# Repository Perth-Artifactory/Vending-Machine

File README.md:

# Vending-Machine
Member can vending machine

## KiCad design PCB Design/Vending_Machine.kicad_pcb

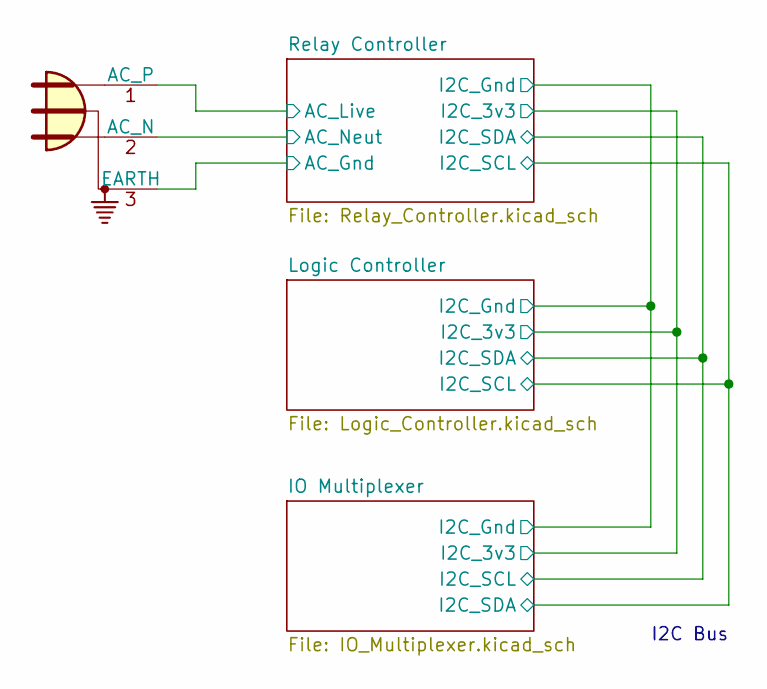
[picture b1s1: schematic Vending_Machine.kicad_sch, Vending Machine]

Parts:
P01: Main Supply

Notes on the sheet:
I2C Bus

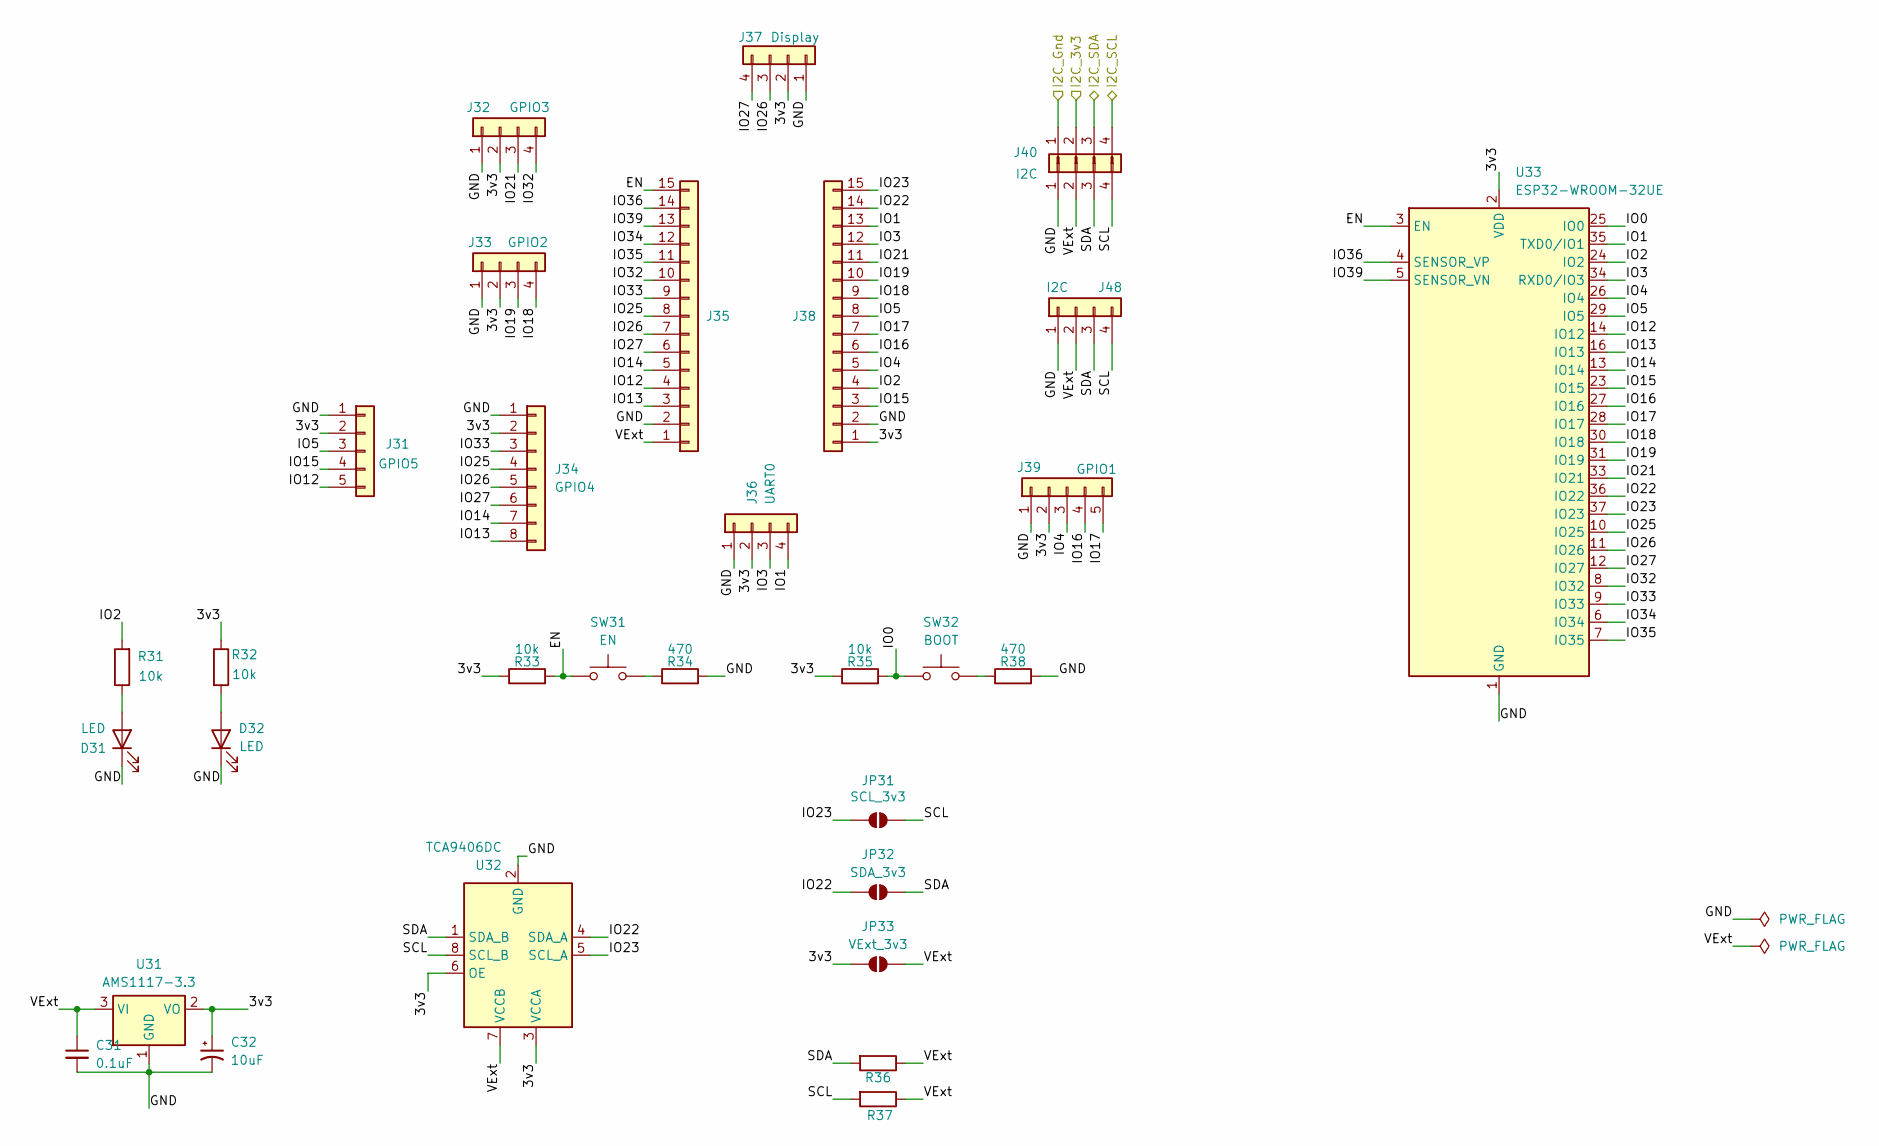
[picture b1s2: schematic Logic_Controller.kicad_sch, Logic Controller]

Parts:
C31: 0.1uF; C_0805_2012Metric_Pad1.18x1.45mm_HandSolder
C32: 10uF; C_0805_2012Metric_Pad1.18x1.45mm_HandSolder
D31, D32: LED; LED_0805_2012Metric_Pad1.15x1.40mm_HandSolder
J31: GPIO5; JST_XH_B5B-XH-A_1x05_P2.50mm_Vertical
J32: GPIO3; JST_XH_B4B-XH-A_1x04_P2.50mm_Vertical
J33: GPIO2; JST_XH_B4B-XH-A_1x04_P2.50mm_Vertical
J34: GPIO4; JST_XH_B8B-XH-A_1x08_P2.50mm_Vertical
J35, J38: Conn_01x15; PinHeader_1x15_P2.54mm_Vertical
J36: UART0; JST_XH_B4B-XH-A_1x04_P2.50mm_Vertical
J37: Display; PinHeader_1x04_P2.54mm_Vertical
J39: GPIO1; JST_XH_B5B-XH-A_1x05_P2.50mm_Vertical
J40, J48: I2C; JST_XH_B4B-XH-A_1x04_P2.50mm_Vertical
J44: Conn_01x04_Pin
JP31: SCL_3v3; SolderJumper-2_P1.3mm_Open_RoundedPad1.0x1.5mm
JP32: SDA_3v3; SolderJumper-2_P1.3mm_Open_RoundedPad1.0x1.5mm
JP33: VExt_3v3; SolderJumper-2_P1.3mm_Open_RoundedPad1.0x1.5mm
R31, R32, R33, R35: 10k; R_0805_2012Metric_Pad1.20x1.40mm_HandSolder
R34, R38: 470; R_0805_2012Metric_Pad1.20x1.40mm_HandSolder
R36, R37: R; R_0805_2012Metric_Pad1.20x1.40mm_HandSolder
SW31: EN; SW_Push_SPST_NO_Alps_SKRK
SW32: BOOT; SW_Push_SPST_NO_Alps_SKRK
U31: AMS1117-3.3; SOT-223-3_TabPin2
U32: TCA9406DC; VSSOP-8_2.3x2mm_P0.5mm
U33: ESP32-WROOM-32UE

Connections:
/Logic Controller/3v3: C32.1, J31.2, J32.2, J33.2, J34.2, J36.2, J37.2, J38.1, J39.2, JP33.1 (A), R32.1, R33.1, R35.1, U31.2 (VO), U32.3 (VCCA), U32.6 (OE), U33.2 (VDD)
/Logic Controller/EN: J35.15, R33.2, SW31.1, U33.3 (EN)
/Logic Controller/GND: C31.2, C32.2, D31.1 (K), D32.1 (K), J31.1, J32.1, J33.1, J34.1, J35.2, J36.1, J37.1, J38.2, J39.1, J40.1, J48.1, R34.2, R38.2, U31.1 (GND), U32.2 (GND), U33.1 (GND), U33.15 (GND), U33.38 (GND), U33.39 (GND); also elsewhere on the board
/Logic Controller/IO0: R35.2, SW32.1, U33.25 (IO0)
/Logic Controller/IO1: J36.4, J38.13, U33.35 (TXD0/IO1)
/Logic Controller/IO2: J38.4, R31.2, U33.24 (IO2)
/Logic Controller/IO3: J36.3, J38.12, U33.34 (RXD0/IO3)
/Logic Controller/IO4: J38.5, J39.3, U33.26 (IO4)
/Logic Controller/IO5: J31.3, J38.8, U33.29 (IO5)
/Logic Controller/IO12: J31.5, J35.4, U33.14 (IO12)
/Logic Controller/IO13: J34.8, J35.3, U33.16 (IO13)
/Logic Controller/IO14: J34.7, J35.5, U33.13 (IO14)
/Logic Controller/IO15: J31.4, J38.3, U33.23 (IO15)
/Logic Controller/IO16: J38.6, J39.4, U33.27 (IO16)
/Logic Controller/IO17: J38.7, J39.5, U33.28 (IO17)
/Logic Controller/IO18: J33.4, J38.9, U33.30 (IO18)
/Logic Controller/IO19: J33.3, J38.10, U33.31 (IO19)
/Logic Controller/IO21: J32.3, J38.11, U33.33 (IO21)
/Logic Controller/IO22: J38.14, JP32.1 (A), U32.4 (SDA_A), U33.36 (IO22)
/Logic Controller/IO23: J38.15, JP31.1 (A), U32.5 (SCL_A), U33.37 (IO23)
/Logic Controller/IO25: J34.4, J35.8, U33.10 (IO25)
/Logic Controller/IO26: J34.5, J35.7, J37.3, U33.11 (IO26)
/Logic Controller/IO27: J34.6, J35.6, J37.4, U33.12 (IO27)
/Logic Controller/IO32: J32.4, J35.10, U33.8 (IO32)
/Logic Controller/IO33: J34.3, J35.9, U33.9 (IO33)
/Logic Controller/IO34: J35.12, U33.6 (IO34)
/Logic Controller/IO35: J35.11, U33.7 (IO35)
/Logic Controller/IO36: J35.14, U33.4 (SENSOR_VP)
/Logic Controller/IO39: J35.13, U33.5 (SENSOR_VN)
/Logic Controller/SCL: J40.4, J48.4, JP31.2 (B), R37.2, U32.8 (SCL_B)
/Logic Controller/SDA: J40.3, J48.3, JP32.2 (B), R36.2, U32.1 (SDA_B)
/Logic Controller/VExt: C31.1, J35.1, J40.2, J48.2, JP33.2 (B), R36.1, R37.1, U31.3 (VI), U32.7 (VCCB)
unnamed: D31.2 (A), R31.1
unnamed: D32.2 (A), R32.2
unnamed: R34.1, SW31.2
unnamed: R38.1, SW32.2

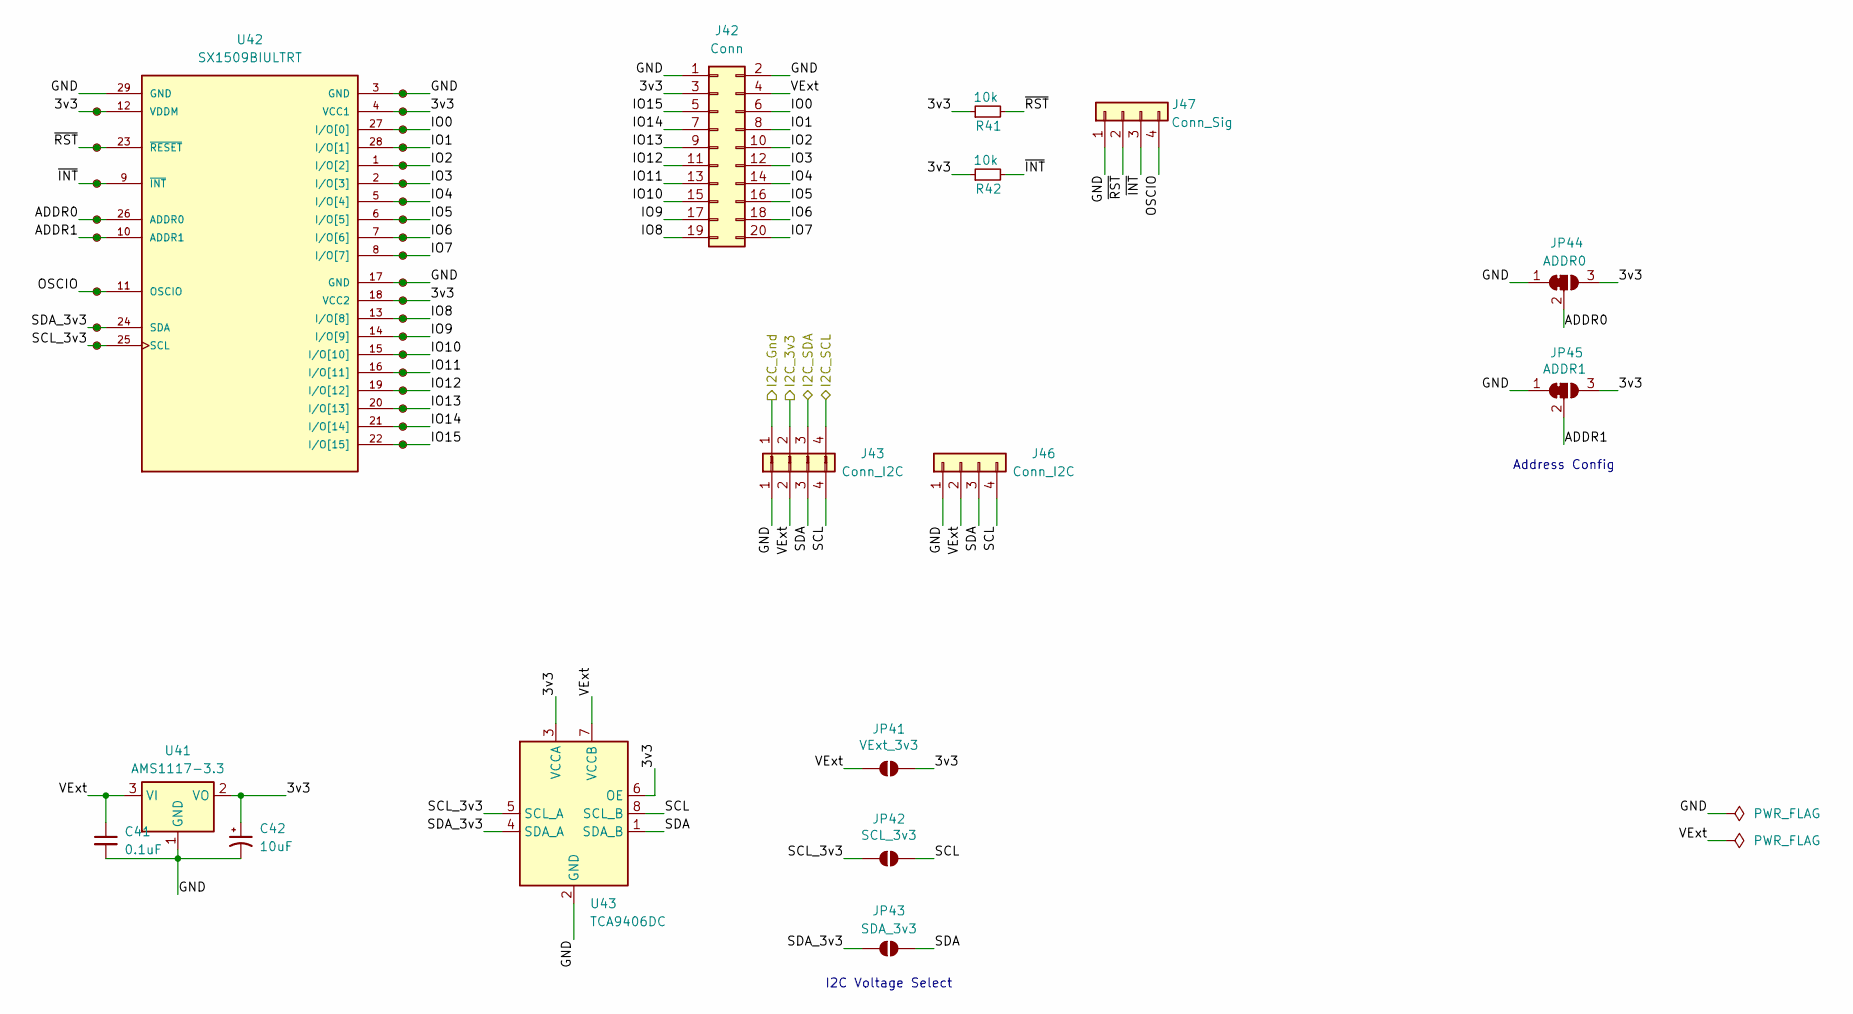
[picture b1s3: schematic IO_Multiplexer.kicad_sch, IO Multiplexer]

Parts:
C41: 0.1uF; C_0805_2012Metric_Pad1.18x1.45mm_HandSolder
C42: 10uF; C_0805_2012Metric_Pad1.18x1.45mm_HandSolder
J42: Conn; IDC-Header_2x10_P2.54mm_Vertical
J43, J46: Conn_I2C; JST_XH_B4B-XH-A_1x04_P2.50mm_Vertical
J45: Conn_01x04_Pin
J47: Conn_Sig; PinHeader_1x04_P2.54mm_Vertical
JP41: VExt_3v3; SolderJumper-2_P1.3mm_Open_RoundedPad1.0x1.5mm
JP42: SCL_3v3; SolderJumper-2_P1.3mm_Open_RoundedPad1.0x1.5mm
JP43: SDA_3v3; SolderJumper-2_P1.3mm_Open_RoundedPad1.0x1.5mm
JP44: ADDR0; SolderJumper-3_P1.3mm_Bridged12_RoundedPad1.0x1.5mm_NumberL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
JP45: ADDR1; SolderJumper-3_P1.3mm_Bridged12_RoundedPad1.0x1.5mm_NumberL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
R41, R42: 10k; R_0805_2012Metric_Pad1.20x1.40mm_HandSolder
TP39, TP48, TP58: 3v3; TestPoint_Pad_D1.0mm
TP40: ~{RST}; TestPoint_Pad_D1.0mm
TP41: ~{INT}; TestPoint_Pad_D1.0mm
TP42: Addr0; TestPoint_Pad_D1.0mm
TP43: Addr1; TestPoint_Pad_D1.0mm
TP44: OSC; TestPoint_Pad_D1.0mm
TP45: SDA; TestPoint_Pad_D1.0mm
TP46: SCL; TestPoint_Pad_D1.0mm
TP47, TP57: GND; TestPoint_Pad_D1.0mm
TP49: IO0; TestPoint_Pad_D1.0mm
TP50: IO1; TestPoint_Pad_D1.0mm
TP51: IO2; TestPoint_Pad_D1.0mm
TP52: IO3; TestPoint_Pad_D1.0mm
TP53: IO4; TestPoint_Pad_D1.0mm
TP54: IO5; TestPoint_Pad_D1.0mm
TP55: IO6; TestPoint_Pad_D1.0mm
TP56: IO7; TestPoint_Pad_D1.0mm
TP59: IO8; TestPoint_Pad_D1.0mm
TP60: IO9; TestPoint_Pad_D1.0mm
TP61: IO10; TestPoint_Pad_D1.0mm
TP62: IO11; TestPoint_Pad_D1.0mm
TP63: IO12; TestPoint_Pad_D1.0mm
TP64: IO13; TestPoint_Pad_D1.0mm
TP65: IO14; TestPoint_Pad_D1.0mm
TP66: IO15; TestPoint_Pad_D1.0mm
U41: AMS1117-3.3; SOT-223-3_TabPin2
U42: SX1509BIULTRT; QFN-28-1EP_4x4mm_P0.4mm_EP2.6x2.6mm_ThermalVias; PARTREV Rev 4 – 26th April 2011
U43: TCA9406DC; VSSOP-8_2.3x2mm_P0.5mm

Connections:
/IO Multiplexer/3v3: C42.1, J42.3, JP41.2 (B), JP44.3 (B), JP45.3 (B), R41.1, R42.1, TP39.1, TP48.1, TP58.1, U41.2 (VO), U42.4 (VCC1), U42.12 (VDDM), U42.18 (VCC2), U43.3 (VCCA), U43.6 (OE)
/IO Multiplexer/ADDR0: JP44.2 (C), TP42.1, U42.26 (ADDR0)
/IO Multiplexer/ADDR1: JP45.2 (C), TP43.1, U42.10 (ADDR1)
/IO Multiplexer/GND: C41.2, C42.2, J42.1, J42.2, J43.1, J46.1, J47.1, JP44.1 (A), JP45.1 (A), TP47.1, TP57.1, U41.1 (GND), U42.3 (GND), U42.17 (GND), U42.29 (GND), U43.2 (GND); also elsewhere on the board
/IO Multiplexer/IO0: J42.6, TP49.1, U42.27 (I/O[0])
/IO Multiplexer/IO1: J42.8, TP50.1, U42.28 (I/O[1])
/IO Multiplexer/IO2: J42.10, TP51.1, U42.1 (I/O[2])
/IO Multiplexer/IO3: J42.12, TP52.1, U42.2 (I/O[3])
/IO Multiplexer/IO4: J42.14, TP53.1, U42.5 (I/O[4])
/IO Multiplexer/IO5: J42.16, TP54.1, U42.6 (I/O[5])
/IO Multiplexer/IO6: J42.18, TP55.1, U42.7 (I/O[6])
/IO Multiplexer/IO7: J42.20, TP56.1, U42.8 (I/O[7])
/IO Multiplexer/IO8: J42.19, TP59.1, U42.13 (I/O[8])
/IO Multiplexer/IO9: J42.17, TP60.1, U42.14 (I/O[9])
/IO Multiplexer/IO10: J42.15, TP61.1, U42.15 (I/O[10])
/IO Multiplexer/IO11: J42.13, TP62.1, U42.16 (I/O[11])
/IO Multiplexer/IO12: J42.11, TP63.1, U42.19 (I/O[12])
/IO Multiplexer/IO13: J42.9, TP64.1, U42.20 (I/O[13])
/IO Multiplexer/IO14: J42.7, TP65.1, U42.21 (I/O[14])
/IO Multiplexer/IO15: J42.5, TP66.1, U42.22 (I/O[15])
/IO Multiplexer/OSCIO: J47.4, TP44.1, U42.11 (OSCIO)
/IO Multiplexer/SCL: J43.4, J46.4, JP42.2 (B), U43.8 (SCL_B)
/IO Multiplexer/SCL_3v3: JP42.1 (A), TP46.1, U42.25 (SCL), U43.5 (SCL_A)
/IO Multiplexer/SDA: J43.3, J46.3, JP43.2 (B), U43.1 (SDA_B)
/IO Multiplexer/SDA_3v3: JP43.1 (A), TP45.1, U42.24 (SDA), U43.4 (SDA_A)
/IO Multiplexer/VExt: C41.1, J42.4, J43.2, J46.2, JP41.1 (A), U41.3 (VI), U43.7 (VCCB)
/IO Multiplexer/~INT: J47.3, R42.2, TP41.1, U42.9 (~INT)
/IO Multiplexer/~RST: J47.2, R41.2, TP40.1, U42.23 (~RESET)

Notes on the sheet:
I2C Voltage Select
Address Config

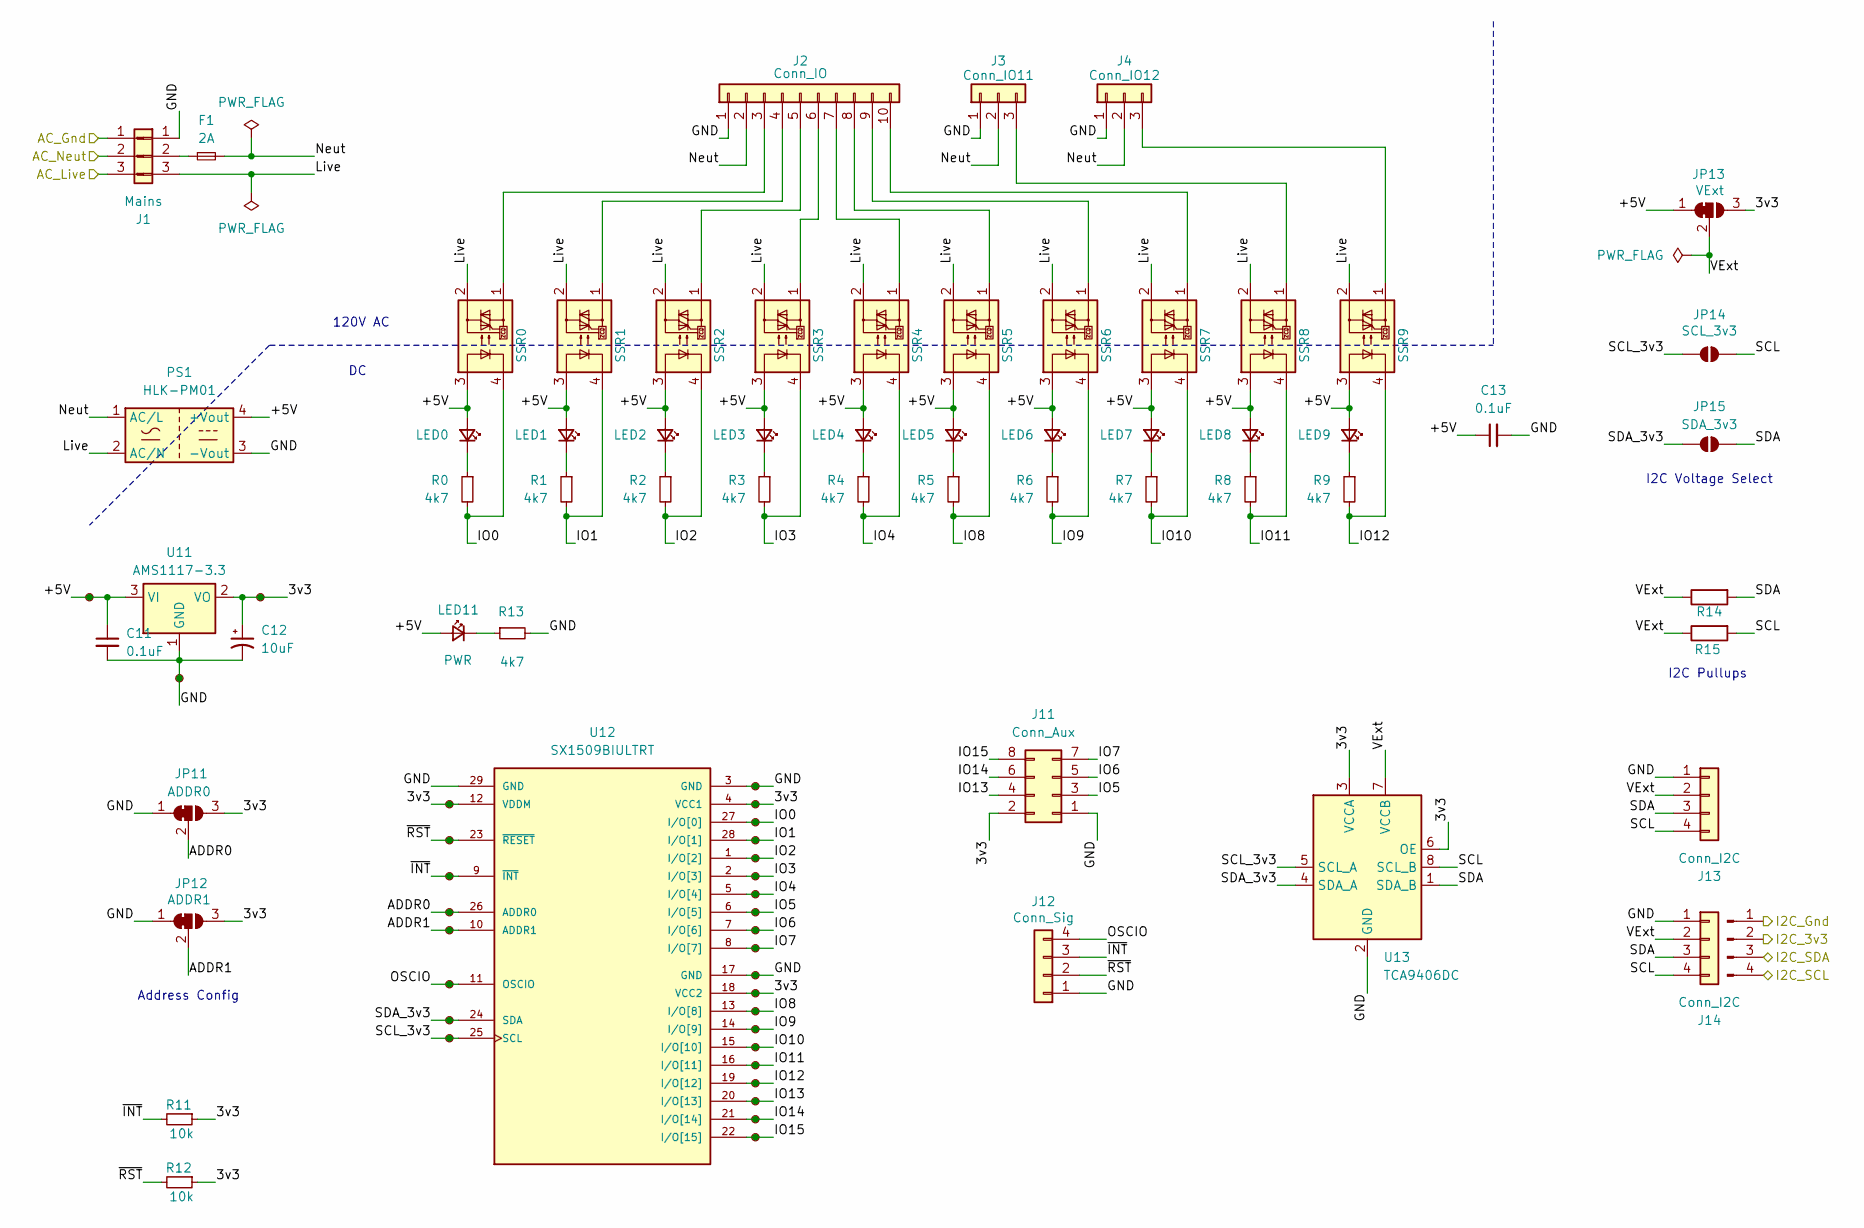
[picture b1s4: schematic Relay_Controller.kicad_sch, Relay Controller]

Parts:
C11, C13: 0.1uF; C_0805_2012Metric_Pad1.18x1.45mm_HandSolder
C12: 10uF; C_0805_2012Metric_Pad1.18x1.45mm_HandSolder
F1: 2A; Fuseholder_5x20mm_15mm_Pins
J1: Mains; PhoenixContact_MC_1,5_3-G-3.81_1x03_P3.81mm_Horizontal
J2: Conn_IO; PhoenixContact_MC_1,5_10-G-3.81_1x10_P3.81mm_Horizontal
J3: Conn_IO11; PhoenixContact_MC_1,5_3-G-3.81_1x03_P3.81mm_Horizontal
J4: Conn_IO12; PhoenixContact_MC_1,5_3-G-3.81_1x03_P3.81mm_Horizontal
J11: Conn_Aux; IDC-Header_2x04_P2.54mm_Vertical
J12: Conn_Sig; JST_XH_B4B-XH-A_1x04_P2.50mm_Vertical
J13, J14: Conn_I2C; JST_XH_B4B-XH-A_1x04_P2.50mm_Vertical
J15: Conn_01x04_Pin
J41: Conn_01x03_Pin
JP11: ADDR0; SolderJumper-3_P1.3mm_Bridged12_RoundedPad1.0x1.5mm_NumberL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
JP12: ADDR1; SolderJumper-3_P1.3mm_Bridged12_RoundedPad1.0x1.5mm_NumberL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
JP13: VExt; SolderJumper-3_P1.3mm_Bridged12_RoundedPad1.0x1.5mm_NumberL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
JP14: SCL_3v3; SolderJumper-2_P1.3mm_Open_RoundedPad1.0x1.5mm
JP15: SDA_3v3; SolderJumper-2_P1.3mm_Open_RoundedPad1.0x1.5mm
LED0, LED1, LED2, LED3, LED4, LED5, LED6, LED7, LED8, LED9: LED_Small; LED_0805_2012Metric_Pad1.15x1.40mm_HandSolder
LED11: PWR; LED_0805_2012Metric_Pad1.15x1.40mm_HandSolder
PS1: HLK-PM01; Converter_ACDC_Hi-Link_HLK-PMxx
R0, R1, R2, R3, R4, R5, R6, R7, R8, R9, R13: 4k7; R_0805_2012Metric_Pad1.20x1.40mm_HandSolder
R11, R12: 10k; R_0805_2012Metric_Pad1.20x1.40mm_HandSolder
R14, R15: R; R_0805_2012Metric_Pad1.20x1.40mm_HandSolder
SSR0, SSR1, SSR2, SSR3, SSR4, SSR5, SSR6, SSR7, SSR8, SSR9: 34.81-8240; RELAY_G3MB202PDC12
TP11: IO2; TestPoint_Pad_D1.0mm
TP12: IO3; TestPoint_Pad_D1.0mm
TP13, TP21, TP28, TP67: 3v3; TestPoint_Pad_D1.0mm
TP14, TP22, TP68: GND; TestPoint_Pad_D1.0mm
TP15: IO4; TestPoint_Pad_D1.0mm
TP16: IO5; TestPoint_Pad_D1.0mm
TP17: IO6; TestPoint_Pad_D1.0mm
TP18: IO7; TestPoint_Pad_D1.0mm
TP19: ~{INT}; TestPoint_Pad_D1.0mm
TP20: ~{RST}; TestPoint_Pad_D1.0mm
TP23: Addr0; TestPoint_Pad_D1.0mm
TP24: Addr1; TestPoint_Pad_D1.0mm
TP25: OSC; TestPoint_Pad_D1.0mm
TP26: SDA; TestPoint_Pad_D1.0mm
TP27: SCL; TestPoint_Pad_D1.0mm
TP29: IO8; TestPoint_Pad_D1.0mm
TP30: IO9; TestPoint_Pad_D1.0mm
TP31: IO10; TestPoint_Pad_D1.0mm
TP32: IO11; TestPoint_Pad_D1.0mm
TP33: IO12; TestPoint_Pad_D1.0mm
TP34: IO13; TestPoint_Pad_D1.0mm
TP35: IO14; TestPoint_Pad_D1.0mm
TP36: IO15; TestPoint_Pad_D1.0mm
TP37: IO0; TestPoint_Pad_D1.0mm
TP38: IO1; TestPoint_Pad_D1.0mm
TP69: 5V; TestPoint_Pad_D1.0mm
U11: AMS1117-3.3; SOT-223-3_TabPin2
U12: SX1509BIULTRT; QFN-28-1EP_4x4mm_P0.4mm_EP2.6x2.6mm_ThermalVias; PARTREV Rev 4 – 26th April 2011
U13: TCA9406DC; VSSOP-8_2.3x2mm_P0.5mm

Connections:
/Relay Controller/3v3: C12.1, J11.2, JP11.3 (B), JP12.3 (B), JP13.3 (B), R11.1, R12.1, TP13.1, TP21.1, TP28.1, TP67.1, U11.2 (VO), U12.4 (VCC1), U12.12 (VDDM), U12.18 (VCC2), U13.3 (VCCA), U13.6 (OE)
/Relay Controller/+5V: C11.1, C13.1, JP13.1 (A), LED0.2 (A), LED1.2 (A), LED2.2 (A), LED3.2 (A), LED4.2 (A), LED5.2 (A), LED6.2 (A), LED7.2 (A), LED8.2 (A), LED9.2 (A), LED11.2 (A), PS1.4 (+Vout), SSR0.3, SSR1.3, SSR2.3, SSR3.3, SSR4.3, SSR5.3, SSR6.3, SSR7.3, SSR8.3, SSR9.3, TP69.1, U11.3 (VI)
/Relay Controller/ADDR0: JP11.2 (C), TP23.1, U12.26 (ADDR0)
/Relay Controller/ADDR1: JP12.2 (C), TP24.1, U12.10 (ADDR1)
/Relay Controller/GND: C11.2, C12.2, C13.2, J1.1, J2.1, J3.1, J4.1, J11.1, J12.1, J13.1, J14.1, JP11.1 (A), JP12.1 (A), PS1.3 (-Vout), R13.2, TP14.1, TP22.1, TP68.1, U11.1 (GND), U12.3 (GND), U12.17 (GND), U12.29 (GND), U13.2 (GND); also elsewhere on the board
/Relay Controller/IO0: R0.2, SSR0.4, TP37.1, U12.27 (I/O[0])
/Relay Controller/IO1: R1.2, SSR1.4, TP38.1, U12.28 (I/O[1])
/Relay Controller/IO2: R2.2, SSR2.4, TP11.1, U12.1 (I/O[2])
/Relay Controller/IO3: R3.2, SSR3.4, TP12.1, U12.2 (I/O[3])
/Relay Controller/IO4: R4.2, SSR4.4, TP15.1, U12.5 (I/O[4])
/Relay Controller/IO5: J11.3, TP16.1, U12.6 (I/O[5])
/Relay Controller/IO6: J11.5, TP17.1, U12.7 (I/O[6])
/Relay Controller/IO7: J11.7, TP18.1, U12.8 (I/O[7])
/Relay Controller/IO8: R5.2, SSR5.4, TP29.1, U12.13 (I/O[8])
/Relay Controller/IO9: R6.2, SSR6.4, TP30.1, U12.14 (I/O[9])
/Relay Controller/IO10: R7.2, SSR7.4, TP31.1, U12.15 (I/O[10])
/Relay Controller/IO11: R8.2, SSR8.4, TP32.1, U12.16 (I/O[11])
/Relay Controller/IO12: R9.2, SSR9.4, TP33.1, U12.19 (I/O[12])
/Relay Controller/IO13: J11.4, TP34.1, U12.20 (I/O[13])
/Relay Controller/IO14: J11.6, TP35.1, U12.21 (I/O[14])
/Relay Controller/IO15: J11.8, TP36.1, U12.22 (I/O[15])
/Relay Controller/Live: J1.3, PS1.2 (AC/N), SSR0.2, SSR1.2, SSR2.2, SSR3.2, SSR4.2, SSR5.2, SSR6.2, SSR7.2, SSR8.2, SSR9.2
/Relay Controller/Neut: F1.2, J2.2, J3.2, J4.2, PS1.1 (AC/L)
/Relay Controller/OSCIO: J12.4, TP25.1, U12.11 (OSCIO)
/Relay Controller/SCL: J13.4, J14.4, JP14.2 (B), R15.2, U13.8 (SCL_B)
/Relay Controller/SCL_3v3: JP14.1 (A), TP27.1, U12.25 (SCL), U13.5 (SCL_A)
/Relay Controller/SDA: J13.3, J14.3, JP15.2 (B), R14.2, U13.1 (SDA_B)
/Relay Controller/SDA_3v3: JP15.1 (A), TP26.1, U12.24 (SDA), U13.4 (SDA_A)
/Relay Controller/VExt: J13.2, J14.2, JP13.2 (C), R14.1, R15.1, U13.7 (VCCB)
/Relay Controller/~INT: J12.3, R11.2, TP19.1, U12.9 (~INT)
/Relay Controller/~RST: J12.2, R12.2, TP20.1, U12.23 (~RESET)
unnamed: F1.1, J1.2
unnamed: J2.3, SSR0.1
unnamed: J2.4, SSR1.1
unnamed: J2.5, SSR2.1
unnamed: J2.6, SSR3.1
unnamed: J2.7, SSR4.1
unnamed: J2.8, SSR5.1
unnamed: J2.9, SSR6.1
unnamed: J2.10, SSR7.1
unnamed: J3.3, SSR8.1
unnamed: J4.3, SSR9.1
unnamed: LED0.1 (K), R0.1
unnamed: LED1.1 (K), R1.1
unnamed: LED2.1 (K), R2.1
unnamed: LED3.1 (K), R3.1
unnamed: LED4.1 (K), R4.1
unnamed: LED5.1 (K), R5.1
unnamed: LED6.1 (K), R6.1
unnamed: LED7.1 (K), R7.1
unnamed: LED8.1 (K), R8.1
unnamed: LED9.1 (K), R9.1
unnamed: LED11.1 (K), R13.1

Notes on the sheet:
120V AC
I2C Pullups
Address Config
I2C Voltage Select

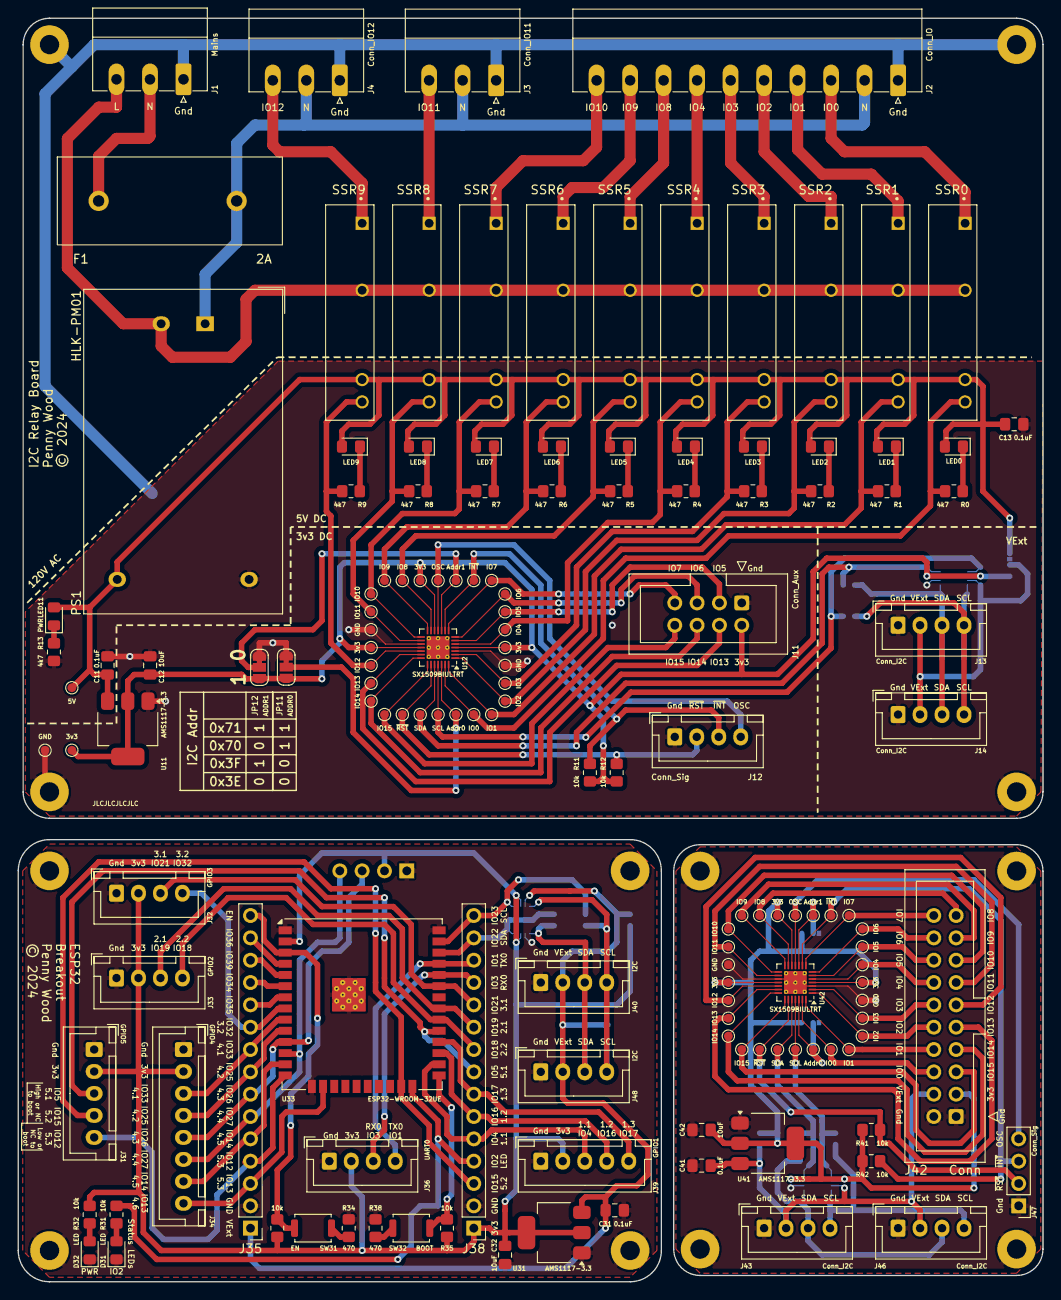
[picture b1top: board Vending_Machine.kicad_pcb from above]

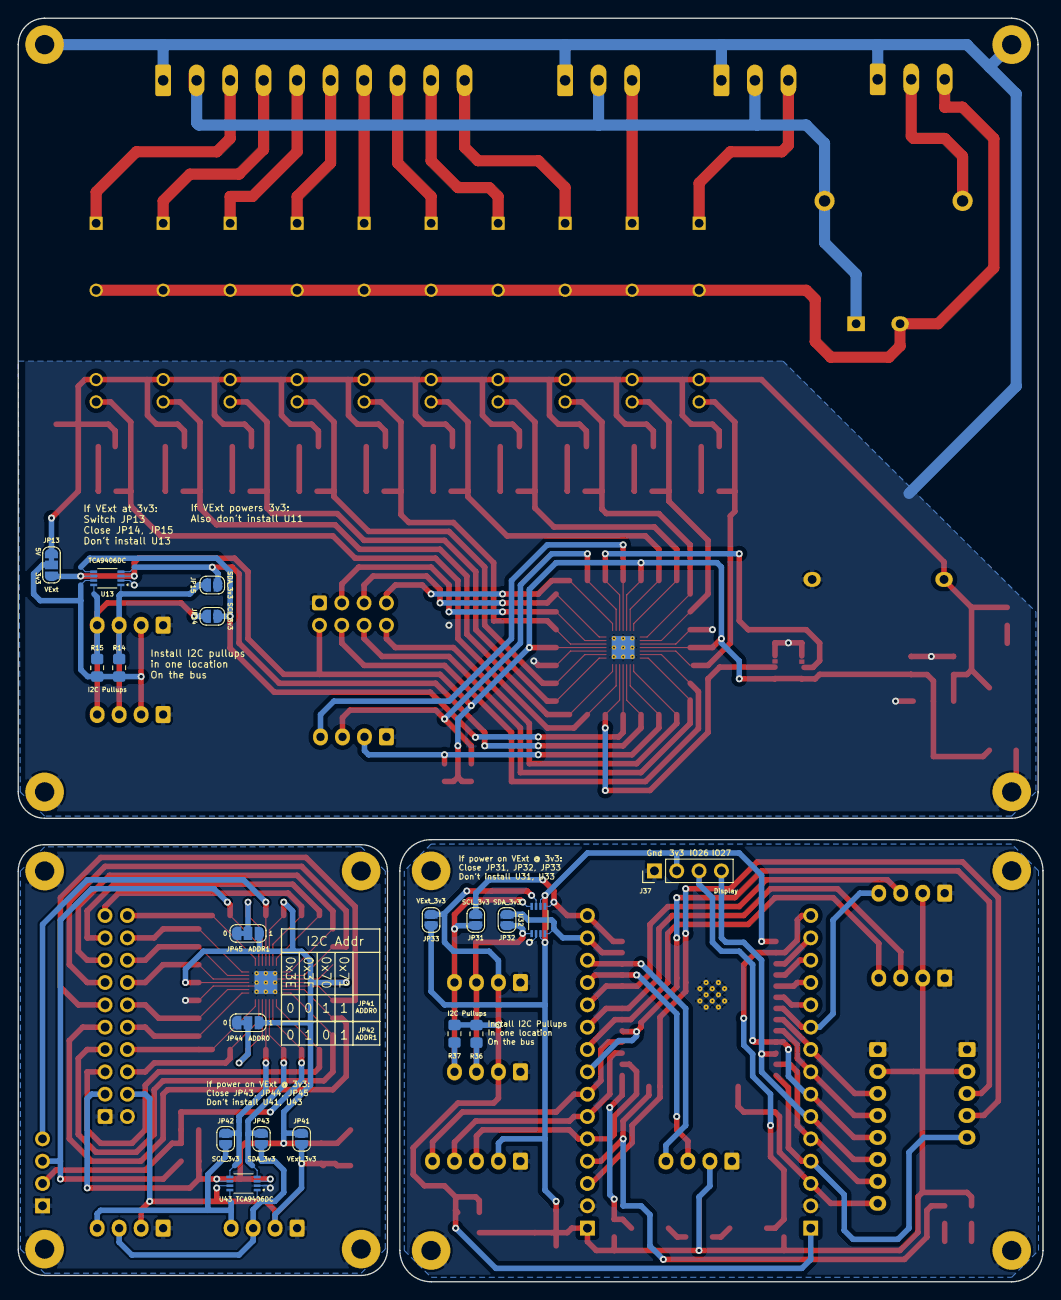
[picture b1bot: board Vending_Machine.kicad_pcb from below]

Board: 2 copper layers, 116.6 x 143.7 mm, 178 parts (19 on the bottom side), 117 nets.

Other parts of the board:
B1: Relay; Board
B2: Controller; Board
B3: Multiplexer; Board
H1, H2, H3, H4, H31, H32, H33, H34, H41, H42, H43, H44: MountingHole_2.2mm_M2_Pad

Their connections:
/IO Multiplexer/GND: H41.1, H42.1, H43.1, H44.1; also elsewhere on the board
/Logic Controller/GND: H31.1, H32.1, H33.1, H34.1; also elsewhere on the board
/Relay Controller/GND: H1.1, H2.1, H3.1, H4.1; also elsewhere on the board

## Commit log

2024-03-29 Controller Board
    Sub board for the controller
2024-03-29 Panelize
2024-03-29 Minor Tweaks
2024-03-29 Moved attributes
2024-03-30 Added Multiplexer
    Added separate IO Multiplexer breakout
2024-03-30 Minor Improvements
2024-03-31 Tweaks and Updates
    Added OSCIO pin to breakout board.
    A few more tweaks
2024-03-31 Updated pages
2024-04-01 SVG Generation
2024-04-04 Add OSCIO pin and voltage section silk-screen
2024-04-04 Add PCB design documentation
2024-04-04 Footnote
2024-04-04 Updated SVGs
2024-04-15 Testpoints to schematic.
2024-04-24 Vcc->3v3 Added extra GPIO
2024-05-06 Ready for production
    Moved connectors to slightly overlap board edge
2024-05-08 Fix layer error
2024-05-20 Fixed silk screens
    Silk screen had incorrect numbering for some pins.

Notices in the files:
PCB Design/Vending_Machine.kicad_pcb:
© 2024
